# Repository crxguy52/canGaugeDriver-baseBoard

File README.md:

Hardware to to use [CANBed FD](https://www.seeedstudio.com/CANBed-FD-Arduino-CAN-FD-Development-Kit-p-4724.html) to read CAN data and drive gauges on a NB Miata

Used in conjunction with the [software](https://github.com/crxguy52/canGaugeDriver)

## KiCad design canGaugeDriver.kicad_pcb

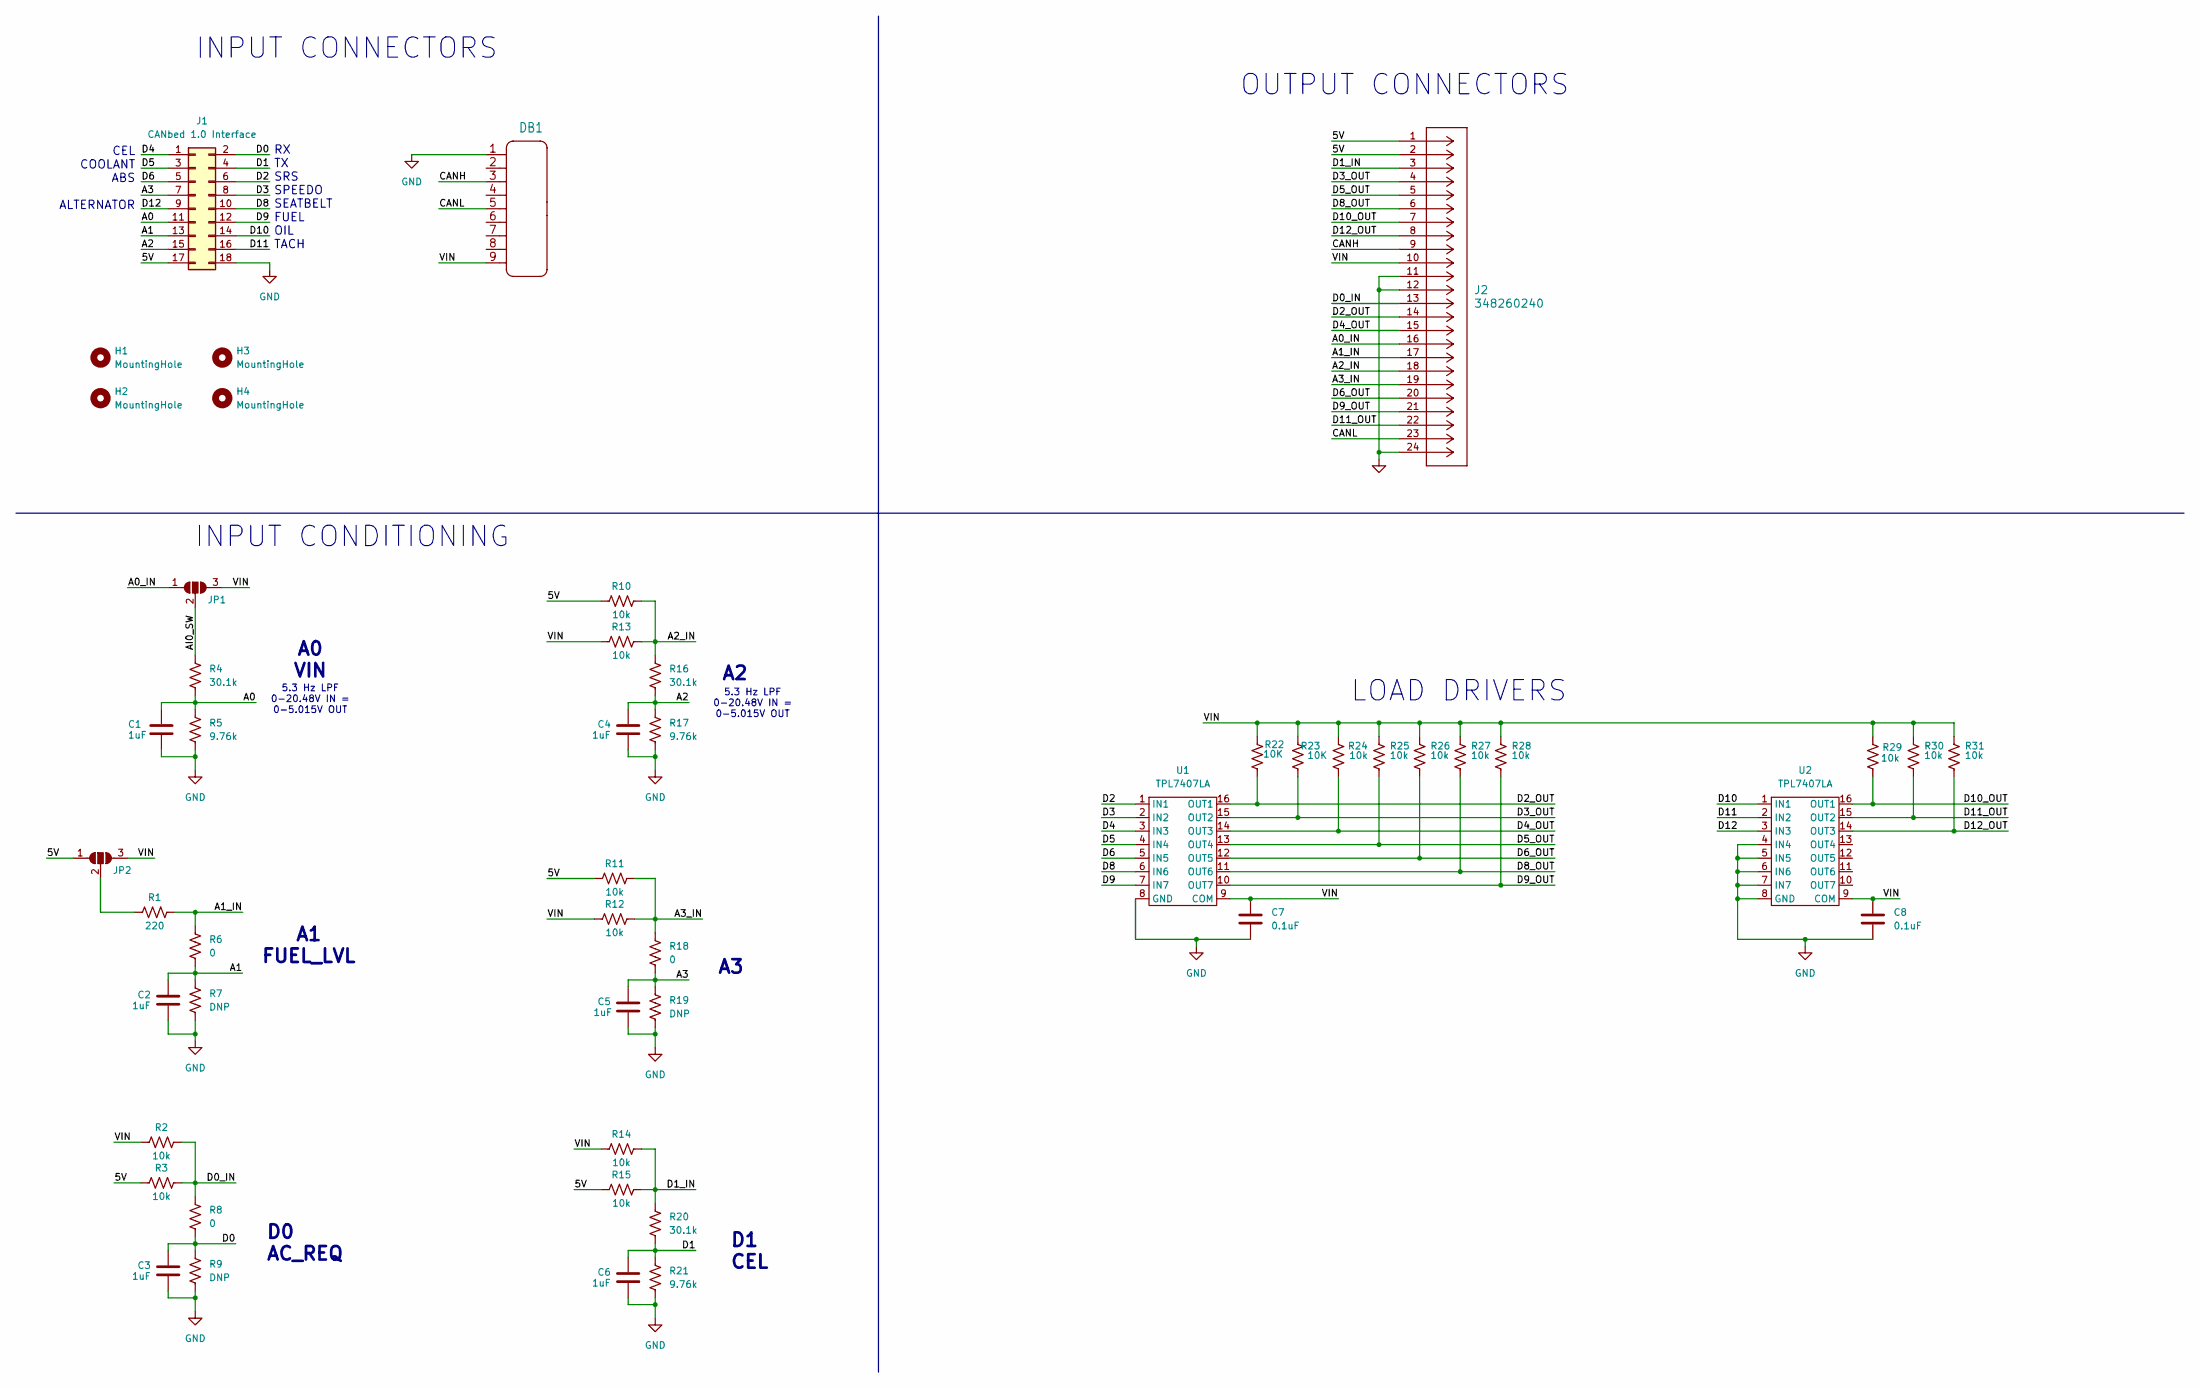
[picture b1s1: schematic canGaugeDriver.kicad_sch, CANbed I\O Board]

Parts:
C1, C2, C3, C4, C5, C6: 1uF; C_0805_2012Metric_Pad1.18x1.45mm_HandSolder
C7, C8: 0.1uF; C_0805_2012Metric_Pad1.18x1.45mm_HandSolder
DB1: DB9'MEAL'; DB9-MEAL
H1, H2, H3, H4: MountingHole; MountingHole_3mm
J1: CANbed 1.0 Interface; PinHeader_2x09_P2.54mm_Vertical
J2: 348260240; CONN_SD-34826-001_24_MOL
JP1, JP2: SolderJumper_3_Open; SolderJumper-3_P1.3mm_Open_Pad1.0x1.5mm_NumberLabels
R1: 220; R_2512_6332Metric
R2, R3, R10, R11, R12, R13, R14, R15, R24, R25, R26, R27, R28, R29, R30, R31: 10k; R_0805_2012Metric_Pad1.20x1.40mm_HandSolder
R4, R16, R20: 30.1k; R_0805_2012Metric_Pad1.20x1.40mm_HandSolder
R5, R17, R21: 9.76k; R_0805_2012Metric_Pad1.20x1.40mm_HandSolder
R6, R8, R18: 0; R_0805_2012Metric_Pad1.20x1.40mm_HandSolder
R7, R9, R19: DNP; R_0805_2012Metric_Pad1.20x1.40mm_HandSolder
R22, R23: 10K; R_0805_2012Metric_Pad1.20x1.40mm_HandSolder
U1, U2: TPL7407LA; SOIC-16_3.9x9.9mm_P1.27mm

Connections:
/5V: J1.17, J2.1, J2.2, JP2.1 (A), R3.2, R10.2, R11.2, R15.2
/A0: C1.1, J1.11, R4.2, R5.1
/A0_IN: J2.16, JP1.1 (A)
/A1: C2.1, J1.13, R6.2, R7.1
/A1_IN: J2.17, R1.1, R6.1
/A2: C4.1, J1.15, R16.2, R17.1
/A2_IN: J2.18, R10.1, R13.1, R16.1
/A3: C5.1, J1.7, R18.2, R19.1
/A3_IN: J2.19, R11.1, R12.1, R18.1
/AI0_SW: JP1.2 (C), R4.1
/CANH: DB1.3, J2.9
/CANL: DB1.5, J2.23
/D0: C3.1, J1.2, R8.2, R9.1
/D0_IN: J2.13, R2.1, R3.1, R8.1
/D1: C6.1, J1.4, R20.2, R21.1
/D1_IN: J2.3, R14.1, R15.1, R20.1
/D2: J1.6, U1.1 (IN1)
/D2_OUT: J2.14, R22.1, U1.16 (OUT1)
/D3: J1.8, U1.2 (IN2)
/D3_OUT: J2.4, R23.2, U1.15 (OUT2)
/D4: J1.1, U1.3 (IN3)
/D4_OUT: J2.15, R24.2, U1.14 (OUT3)
/D5: J1.3, U1.4 (IN4)
/D5_OUT: J2.5, R25.2, U1.13 (OUT4)
/D6: J1.5, U1.5 (IN5)
/D6_OUT: J2.20, R26.2, U1.12 (OUT5)
/D8: J1.10, U1.6 (IN6)
/D8_OUT: J2.6, R27.2, U1.11 (OUT6)
/D9: J1.12, U1.7 (IN7)
/D9_OUT: J2.21, R28.2, U1.10 (OUT7)
/D10: J1.14, U2.1 (IN1)
/D10_OUT: J2.7, R29.2, U2.16 (OUT1)
/D11: J1.16, U2.2 (IN2)
/D11_OUT: J2.22, R30.2, U2.15 (OUT2)
/D12: J1.9, U2.3 (IN3)
/D12_OUT: J2.8, R31.2, U2.14 (OUT3)
/VIN: C7.1, C8.1, DB1.9, J2.10, JP1.3 (B), JP2.3 (B), R2.2, R12.2, R13.2, R14.2, R22.2, R23.1, R24.1, R25.1, R26.1, R27.1, R28.1, R29.1, R30.1, R31.1, U1.9 (COM), U2.9 (COM)
GND: C1.2, C2.2, C3.2, C4.2, C5.2, C6.2, C7.2, C8.2, DB1.1, J1.18, J2.11, J2.12, J2.24, R5.2, R7.2, R9.2, R17.2, R19.2, R21.2, U1.8 (GND), U2.4 (IN4), U2.5 (IN5), U2.6 (IN6), U2.7 (IN7), U2.8 (GND)
unnamed: JP2.2 (C), R1.2

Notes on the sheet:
D0 AC_REQ
5.3 Hz LPF 0-20.48V IN = 0-5.015V OUT
INPUT CONNECTORS
INPUT CONDITIONING
RX TX SRS SPEEDO SEATBELT FUEL OIL TACH
A0 VIN
LOAD DRIVERS
D1 CEL
OUTPUT CONNECTORS
CEL COOLANT ABS ALTERNATOR
A1 FUEL_LVL

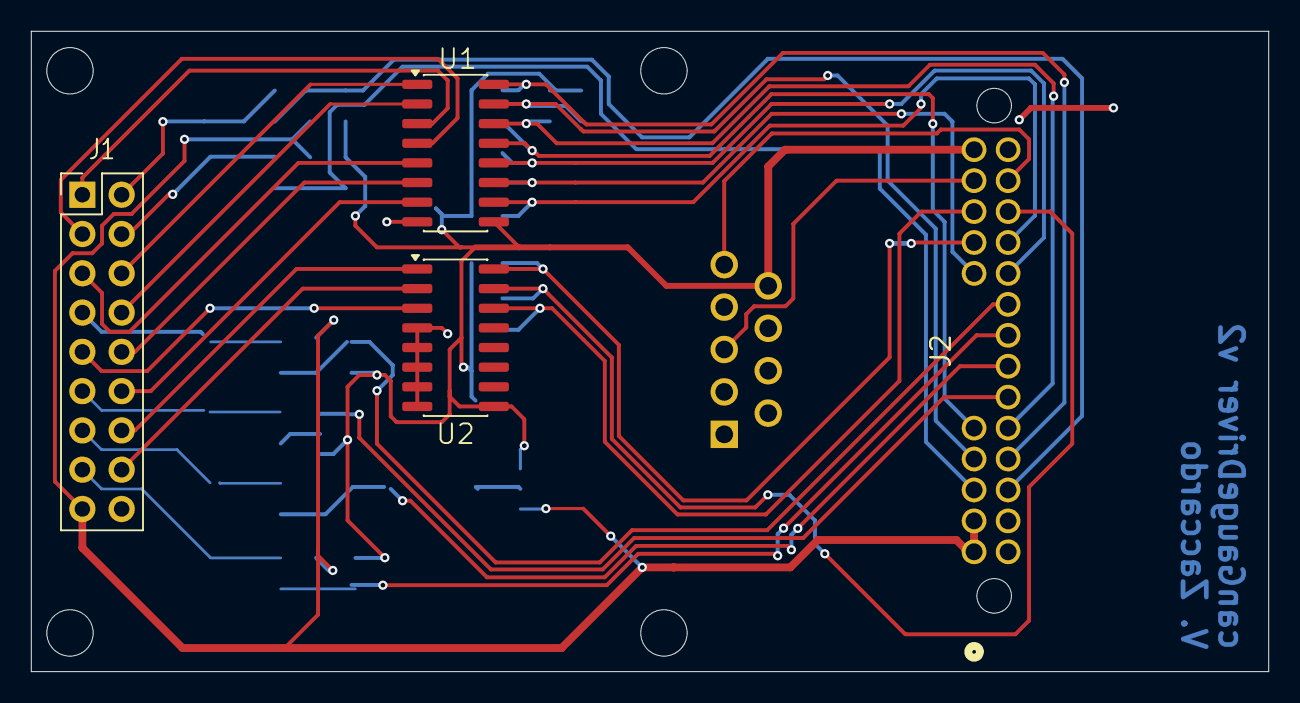
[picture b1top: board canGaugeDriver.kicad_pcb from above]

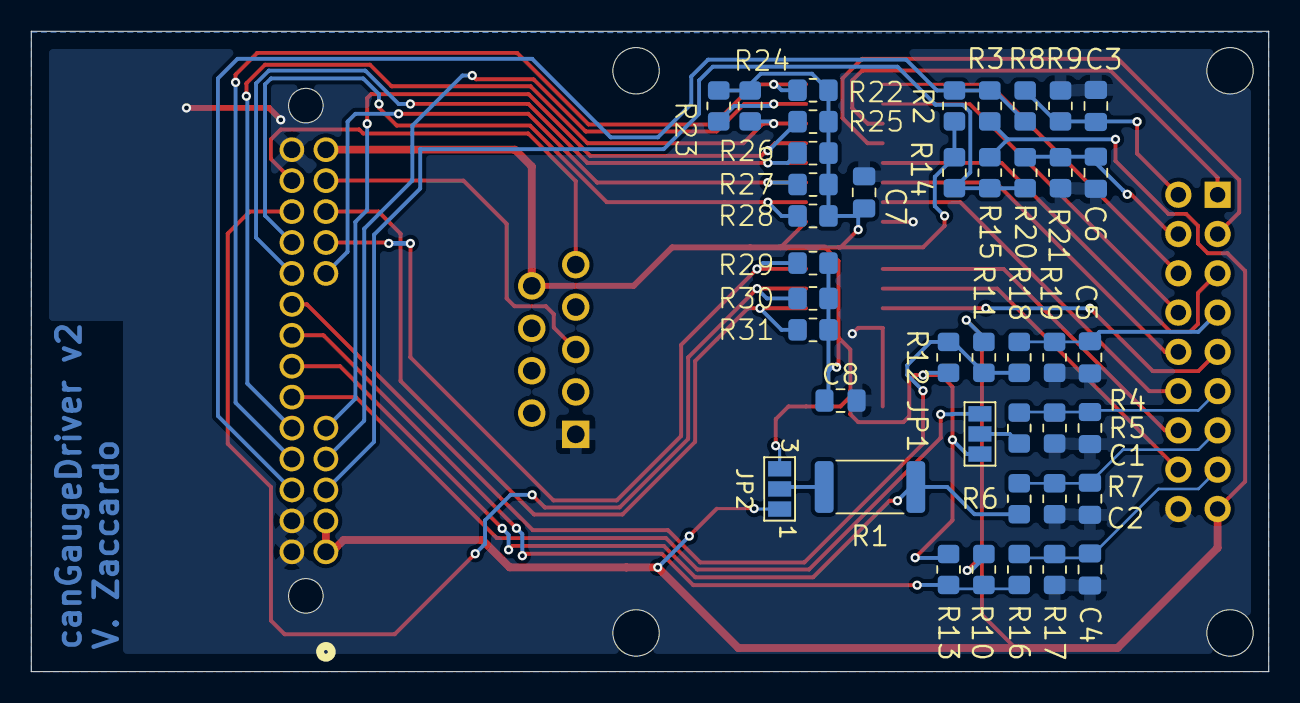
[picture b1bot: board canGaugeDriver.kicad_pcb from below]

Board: 2 copper layers, 80.0 x 41.4 mm, 50 parts (41 on the bottom side), 39 nets.

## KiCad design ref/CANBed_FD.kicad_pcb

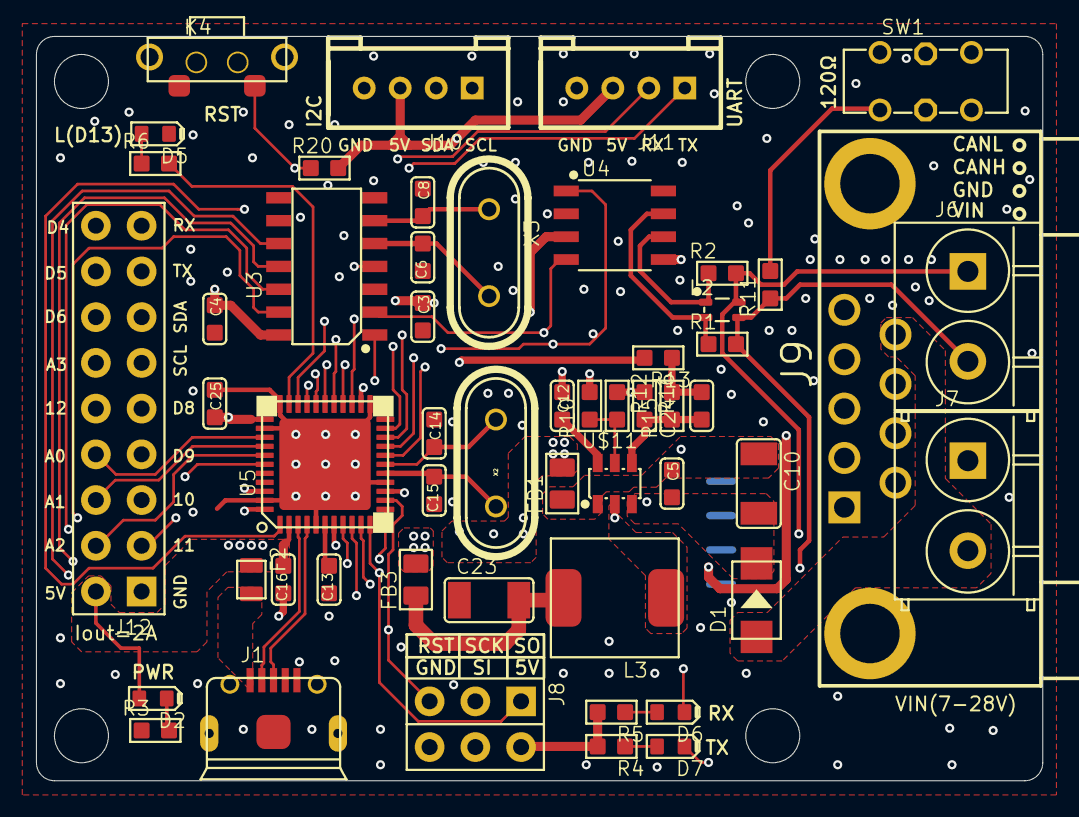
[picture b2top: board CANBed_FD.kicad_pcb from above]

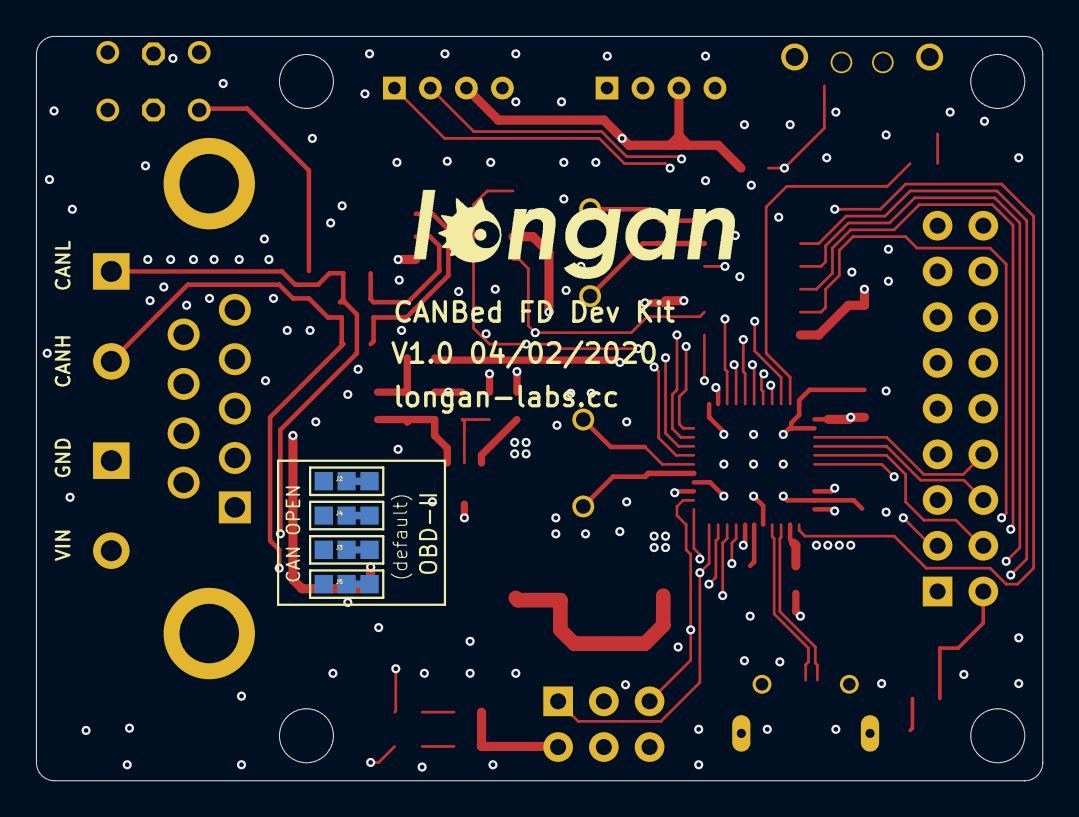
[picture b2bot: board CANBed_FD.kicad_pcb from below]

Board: 6 copper layers, 55.9 x 41.4 mm, 62 parts (5 on the bottom side), 58 nets.

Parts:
C3, C4, C5, C12, C13, C16, C25: 100nF; C0603
C6, C8, C14, C15: 22pF; C0603
C10: 4.7uF; C1206
C23: 22uF; C1206
C24: 75pF; C0603
D1: SS32; DO-214AC
D2: green; LED-0603
D5: blue; LED-0603
D6, D7: RED; LED-0603
F2: 0805L100WR; F0805
FB1, FB3: 0R; F0805
J1: MICRO-USB5+5P-SMD-0.65-7.2X5.06MM
J2, J3, J4, J5: JUMPER-3P-SHORT; 3P-SMD-SHORT
J6, J7: H2-5.0-10.5X8.0MM
J8: H2X3-2.54
J9: DB9-MEAL
J10, J11: 320110033; HW4-2.0
J12: H2X9-2.54
K4: SW2+2P-7.7X2.75X3.95MM
L2: DNP; INT4-0.85-2X1.25X1.2MM
L3: 10uH; INT2-SMD-6.6X7.1X3MM
R1, R2: 0R; R0603
R3, R4, R5, R6: 1k; R0603
R10: 560k/1%]; R0603
R11: 120R; R0603
R12, R15: 100k/1%; R0603
R13: 49.9R; R0603
R16: 13.3k; R0603
R20: 10k; R0603
SW1: SW6-2.54-9.0X3.5X3.2+2.0MM
U3: SOIC14-1.27-8.6X3.9MM
U4: SOIC8-1.27-5X4MM
U5: ATMEGA32U4-MU; QFN44
U$11: PMIC-TPS54302; SOT-23-6
U$12: LONGAN-SILK-SMALL
UNK_HOLE_0: dummyfp0
UNK_HOLE_1: dummyfp1
UNK_HOLE_2: dummyfp2
UNK_HOLE_3: dummyfp3
X2: 16MHz; HC49US
X3: 20MHz; HC49US

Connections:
A0: J12.15, U5.36
A1: J12.16, U5.37
A2: J12.17, U5.38
A3: J12.13, U5.39
AGND: C5.1, C10.1, FB1.1, R12.1, R16.1, U$11.1
CAN+: L2.4, R1.1, U4.7
CAN-: L2.1, R2.1, U4.6
CANH: J3.MM, J6.2, L2.3, R1.2, R11.1
CANL: J4.MM, J6.1, L2.2, R2.2, SW1.COM1
D4: J12.10, U5.25
D5: J12.11, U5.31
D6: J12.12, U5.27
D8: J12.5, U5.28
D9: J12.4, U5.29
D10: J12.3, U5.30
D11: J12.2, U5.12
D12: J12.14, U5.26
D13: R6.2, U5.32
D17: U3.13, U5.8
EXT_PWR: F2.2, J1.1
GND: C3.2, C4.2, C6.1, C8.1, C13.1, C14.1, C15.1, C16.1, C23.1, C25.1, D5.-, FB1.2, J1.5, J1.P1, J1.P3, J1.P4, J1.P5, J1.P6, J2.MM, J5.MM, J7.1, J8.4, J9.G1, J9.G2, J10.4, J11.4, J12.1, K4.1, K4.S1, K4.S2, R3.1, U3.7, U4.2, U4.8, U5.5, U5.15, U5.23, U5.33, U5.35, U5.43, U5.TAB
INT: U3.4, U5.1
MISO: J8.1, U3.12, U5.11
MOSI: J8.5, U3.11, U5.10
unnamed: D2.-, R3.2
unnamed: D7.+, R4.1
unnamed: R10.1, R12.2, U$11.5
unnamed: C14.2, U5.17, X2.2
unnamed: D5.+, R6.1
unnamed: C6.2, U3.5, X3.2
unnamed: C12.1, L3.1, U$11.2
unnamed: C15.2, U5.16, X2.1
unnamed: J5.11, J9.1
unnamed: C12.2, U$11.6
unnamed: D6.+, R5.1
unnamed: R11.2, SW1.CH1A
unnamed: C8.2, U3.6, X3.1
unnamed: C23.2, FB3.1, L3.2
unnamed: C24.2, R13.1, R15.2
unnamed: C24.1, R15.1, R16.2, U$11.4
PIN2: J2.11, J4.00, J9.2
PIN3: J2.00, J3.11, J9.3
PIN5: J4.11, J9.5
PIN7: J3.00, J9.7
RESET: J8.3, K4.2, R20.1, U5.13
RX: J11.2, J12.9, U5.20
RX_CAN: D6.-, U3.2, U4.4
SCK: J8.2, U3.10, U5.9
SCL: J10.1, J12.6, U5.18
SDA: J10.2, J12.7, U5.19
TX: J11.1, J12.8, U5.21
TX_CAN: D7.-, U3.1, U4.1
UCAP: C13.2, U5.6
USB+: J1.3, U5.4
USB-: J1.2, U5.3
VCC_5V: C3.1, C4.1, C16.2, C25.2, D2.+, F2.1, FB3.2, J8.6, J10.3, J11.3, J12.18, R4.2, R5.2, R13.2, R20.2, U3.14, U4.3, U4.5, U5.2, U5.7, U5.14, U5.24, U5.34, U5.42, U5.44
VIN: D1.1, J7.2, J9.9
VIN_12V: C5.2, C10.2, D1.2, R10.2, U$11.3
